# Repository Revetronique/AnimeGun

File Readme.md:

# アニメ銃 (ストロボスコープ式映写機)

## 目次
- [アニメ銃 (ストロボスコープ式映写機)](#アニメ銃-ストロボスコープ式映写機)
  - [目次](#目次)
- [概要](#概要)
- [準備するもの](#準備するもの)
  - [本体](#本体)
  - [円板](#円板)
- [使い方](#使い方)
  - [ボタン一覧](#ボタン一覧)
  - [基本](#基本)
  - [詳細](#詳細)
    - [パラメータ設定](#パラメータ設定)
    - [設定モード](#設定モード)
    - [設定方法](#設定方法)
    - [ファームウェア書き換え](#ファームウェア書き換え)
- [免責事項](#免責事項)
- [開発者](#開発者)
# 概要
影絵でアニメーション映像を見せる映写機です。

電源を入れて、壁に向かって引き金のボタンを押すことで、壁にアニメーションが映し出されます。

アニメのコマを描いた円板をモーターで回し、LEDのストロボ発光でアニメーションを移す仕組みです。
# 準備するもの
## 本体
- Arduino UNO R3
- LED
  - 単色を想定(主に白色)
  - パワーLED(5V, 1W or 3W)にも対応
- 専用シールド
  - [回路およびプリント基板(Eagle用)](./Circuit)
  - 回路の詳細については、[回路についてのドキュメント](./Docs/Document_Circuit.md)を参照
- 筐体
  - アクリル板(厚さ3mm)をレーザーカッターで切断して、各パーツを積み重ねて制作
  - 筐体用のフレームは[Frameフォルダ](./Frame)を参照
  - 詳細は、[筐体についてのドキュメント](./Docs/Document_Frame.md)を参照
  - **試作段階のため、回路が筐体に収まらないなどの問題が生じる可能性があります**
- ACアダプタ(出力：DC12V, 1A以上)
## 円板
詳細は[円板についてのドキュメント](./Docs/Document_Plate.md)を参照。
# 使い方

## ボタン一覧
1. **トリガー**：押すことでアニメを動かします(ストロボ発光+モーター駆動)
2. 7セグLED：設定モード([後述](#設定モード))やアニメに関するパラメータを表示
3. 機能ボタン：押すと設定モードを変更
4. **調節ノブ**：回すことでパラメータを調節

また、トグルスイッチでモーター回転の有効/無効を切り替えられます(右に倒すと有効)。ファームウェアの書き換え中など、モーターを回したくない時は左に倒してください。
## 基本
1. モーターにアニメ用の円板を付けます
2. 本体後ろのDCジャックに、上記のACアダプタから電源を供給
3. 銃口を壁に向けてトリガーを引くと、アニメーションが流れます
4. 調節ノブを回すと、アニメーションの速さを変えられます
## 詳細
### パラメータ設定
機能ボタンと調節ノブを使って、アニメーションに関する4種類のパラメータを調整できます。選択したパラメータと数値は7セグLEDで確認できます。
### 設定モード
パラメータの種類は以下の通り。
- sp(回転速度)：モーターの回転数(rpm)。数値は8~60
- dg(角度調節)：円板の角度調節。ずれの相殺に使います
- br(明るさ)：LEDの明るさ調整。0~25までの26段階
- fr(フレーム数)：アニメのコマ数
### 設定方法
起動時は、sp(回転速度)がセットされています。

ボタンを押すと、sp->dg->bf->fr の順に切り替わります。ボタンを押して0.5秒程度、選んだパラメータ名が7セグLEDに表示されます。

表示が数値に切り替わったら、調節ノブでパラメータを調節できます。
### ファームウェア書き換え
本体のファームウェア(Arduinoスケッチ)を書き換えたい場合は、背面のUSBコネクタでArduino IDEの入ったPCなどと接続します。ケーブルはUSB(ABタイプ)を使用します。
# 免責事項
- **使うときは人に向けないでください。特にパワーLEDを搭載する場合、失明の恐れがあります**
- 本体を振り回さないでください。ケガや破損の恐れがあります。
- モーターの回転中は、円板に触れないよう注意してください。思わぬケガの元となります。
- ファームウェア書き換え時は、書き込み用の機器と接続する前に、本体の電源を外してください。また、**接続中はトリガーを押さないでください**。
- 円板を付け替える際も、電源を外してから作業してください。
- 15V以上の電圧を絶対にかけないでください。
  - 出力電源は、12V,1A出力のACアダプタ推奨。
- 上記の項目の他、組み立て時や使用中などにおける利用者のあらゆる事故・不具合に対して、開発者は責任を負いません。

# 開発者
Revetronique
- [Web](https://revetronique.com/)
- [Twitter](https://twitter.com/Revetronique)
- [Instagram](https://www.instagram.com/revetronique/)

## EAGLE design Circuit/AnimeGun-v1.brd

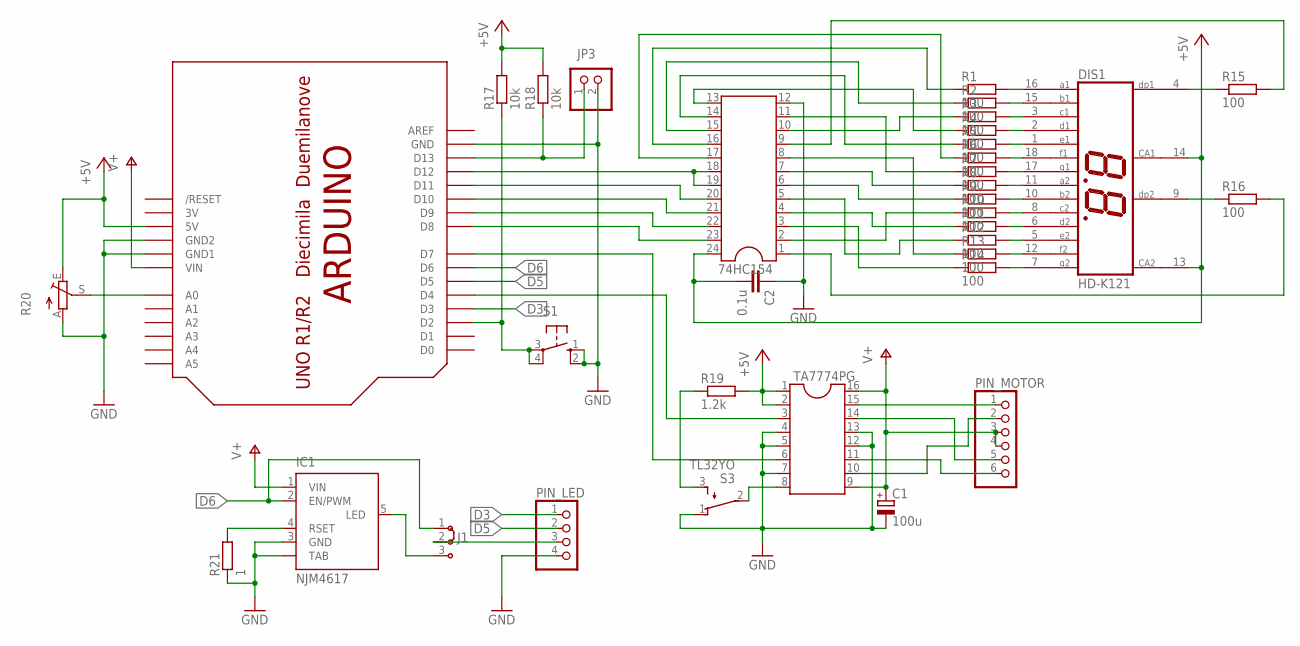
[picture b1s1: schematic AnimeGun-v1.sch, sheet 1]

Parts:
74HC154: DIL24-3
C1: 100u; 153CLV-0605
C2: 0.1u; C0603
DIS1: HD-K121; HDSP-R
IC1: NJM4617; TO263_5
J1: J2X2MM; 04C
JP3: PINHD-1X2; 1X02
PIN_LED: PINHD-1X4/90; 1X04/90
PIN_MOTOR: PINHD-1X6/90; 1X06/90
R1, R2, R3, R4, R5, R6, R7, R8, R9, R10, R12, R13, R14, R15, R16: 100; R0603
R11: R-EU_R0603; R0603
R17, R18: 10k; R0603
R19: 1.2k; R0603
R20: TRIM_EU-B25U; B25U
R21: 1; R0603
S1: 10-XX; B3F-10XX
S3: TL32YO; TL3XYO
TA7774PG: DIL16
U1: ARDUINO-NOHOLE

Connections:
3V: U1.3V
+5V: 74HC154.24, C2.2, DIS1.13 (CA2), DIS1.14 (CA1), R17.2, R18.2, R19.2, R20.E, TA7774PG.1, TA7774PG.2, U1.5V
D3: PIN_LED.1, U1.D3
D5: PIN_LED.2, U1.D5
D6: IC1.2 (EN/PWM), J1.1, U1.D6
GND: 74HC154.12, C1.-, C2.1, IC1.3 (GND), IC1.TAB, JP3.2, PIN_LED.4, R20.A, R21.1, S1.1 (S), S1.2 (S1), S3.1 (O), TA7774PG.4, TA7774PG.5, TA7774PG.7, TA7774PG.12, TA7774PG.13, U1.GND, U1.GND1, U1.GND2
unnamed: R17.1, S1.3, S1.4 (P1), U1.D2
unnamed: DIS1.16 (A1), R1.2
unnamed: DIS1.15 (B1), R2.2
unnamed: DIS1.3 (C1), R3.2
unnamed: DIS1.2 (D1), R4.2
unnamed: DIS1.1 (E1), R5.2
unnamed: DIS1.18 (F1), R6.2
unnamed: DIS1.17 (G1), R7.2
unnamed: DIS1.11 (A2), R8.2
unnamed: DIS1.10 (B2), R9.2
unnamed: DIS1.8 (C2), R10.2
unnamed: DIS1.6 (D2), R11.2
unnamed: DIS1.5 (E2), R12.2
unnamed: DIS1.12 (F2), R13.2
unnamed: DIS1.7 (G2), R14.2
unnamed: DIS1.4 (DP1), R15.1
unnamed: DIS1.9 (DP2), R16.1
unnamed: 74HC154.1, R16.2
unnamed: 74HC154.2, R10.1
unnamed: 74HC154.3, R14.1
unnamed: 74HC154.4, R11.1
unnamed: 74HC154.5, R12.1
unnamed: 74HC154.6, R9.1
unnamed: 74HC154.7, R8.1
unnamed: 74HC154.8, R13.1
unnamed: 74HC154.9, R15.2
unnamed: 74HC154.10, R3.1
unnamed: 74HC154.11, R7.1
unnamed: 74HC154.13, R4.1
unnamed: 74HC154.14, R5.1
unnamed: 74HC154.15, R2.1
unnamed: 74HC154.16, R1.1
unnamed: 74HC154.17, R6.1
unnamed: 74HC154.18, 74HC154.19, U1.D12
unnamed: TA7774PG.6, U1.D7
unnamed: 74HC154.20, U1.D11
unnamed: 74HC154.21, U1.D10
unnamed: 74HC154.22, U1.D9
unnamed: 74HC154.23, U1.D8
unnamed: TA7774PG.3, U1.D4
unnamed: JP3.1, R18.1, U1.D13
unnamed: S3.2, TA7774PG.8
unnamed: PIN_MOTOR.6, TA7774PG.11
unnamed: PIN_MOTOR.1, TA7774PG.15
unnamed: PIN_MOTOR.5, TA7774PG.14
unnamed: PIN_MOTOR.2, TA7774PG.10
unnamed: R19.1, S3.3 (S)
unnamed: R20.S, U1.A0
unnamed: IC1.4 (RSET), R21.2
unnamed: J1.2, PIN_LED.3
unnamed: IC1.5 (LED), J1.3
V+: C1.+, IC1.1 (VIN), PIN_MOTOR.3, PIN_MOTOR.4, TA7774PG.9, TA7774PG.16, U1.VIN

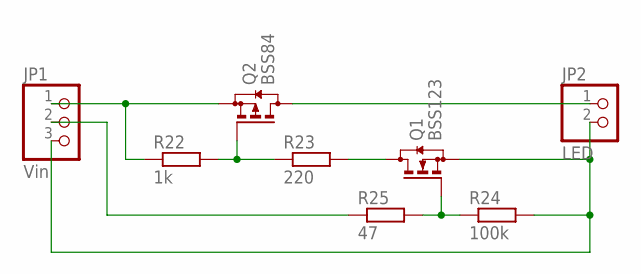
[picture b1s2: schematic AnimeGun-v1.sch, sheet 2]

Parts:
JP1: Vin; 1X03
JP2: LED; 1X02
Q1: BSS123; SOT23
Q2: BSS84; SOT23
R22: 1k; R2512
R23: 220; R2512
R24: 100k; R0603
R25: 47; R0603

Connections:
unnamed: Q2.1 (G), R22.2, R23.1
unnamed: JP1.1, Q2.2 (S), R22.1
unnamed: Q1.3 (D), R23.2
unnamed: JP2.1, Q2.3 (D)
unnamed: Q1.1 (G), R24.1, R25.2
unnamed: JP1.3, JP2.2, Q1.2 (S), R24.2
unnamed: JP1.2, R25.1

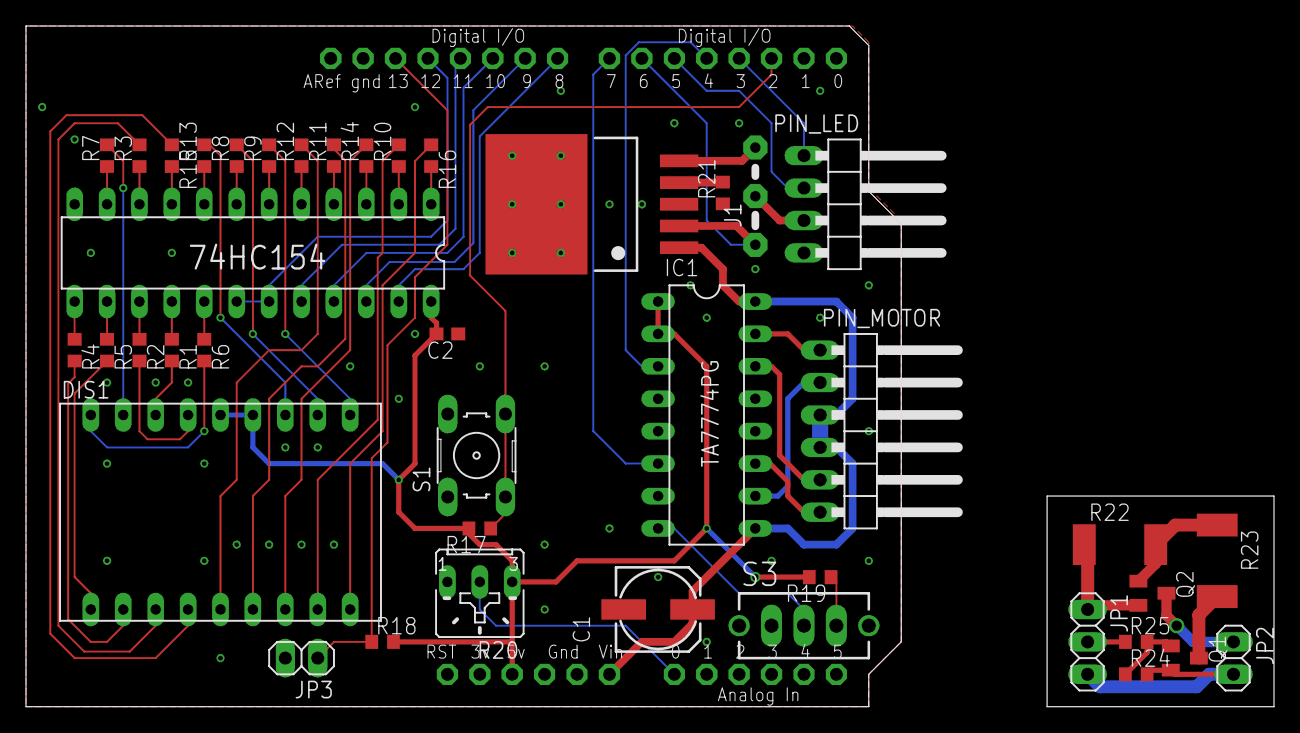
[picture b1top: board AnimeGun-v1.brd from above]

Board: 2 copper layers, 97.8 x 53.3 mm, 42 parts (0 on the bottom side), 64 nets.

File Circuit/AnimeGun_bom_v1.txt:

Partlist exported from C:/Users/kokit/OneDrive/ドキュメント/EAGLE/projects/AnimeGun/AnimeGun-v1.sch at 2020/11/28 15:33

Part      Value          Device             Package        Description                                     MF MPN           OC_FARNELL OC_NEWARK POPULARITY SPICEPREFIX
74HC154                  DIL24-3            DIL24-3        Dual In Line                                                                          0                     
C1        100u           CPOL-EU153CLV-0605 153CLV-0605    POLARIZED CAPACITOR, European symbol                                                  5          C          
C2        0.1u           C-EUC0603          C0603          CAPACITOR, European symbol                                                            73         C          
DIS1      HD-K121        HD-K121            HDSP-R         LED DISPLAY                                                      unknown    unknown   0                     
IC1       NJM4617        NJM4617            TO263_5        1A Constant-Current LED Driver with PWM Dimming    CAT4101TV-T75 1718452    08R5264                         
J1                       J2X2MM             04C            Jumper switch 2 x 2.5 mm                                                                                    
JP1       Vin            PINHD-1X3          1X03           PIN HEADER                                                                            92                    
JP2       LED            PINHD-1X2          1X02           PIN HEADER                                                                            98                    
JP3                      PINHD-1X2          1X02           PIN HEADER                                                                            98                    
PIN_LED                  PINHD-1X4/90       1X04/90        PIN HEADER                                                                            9                     
PIN_MOTOR                PINHD-1X6/90       1X06/90        PIN HEADER                                                                            10                    
Q1        BSS123         BSS123             SOT23          N-CHANNEL MOS FET                                                                                           
Q2        BSS84          BSS84              SOT23          P-CHANNEL MOS FET                                                                                           
R1        100            R-EU_R0603         R0603          RESISTOR, European symbol                                                             70         R          
R2        100            R-EU_R0603         R0603          RESISTOR, European symbol                                                             70         R          
R3        100            R-EU_R0603         R0603          RESISTOR, European symbol                                                             70         R          
R4        100            R-EU_R0603         R0603          RESISTOR, European symbol                                                             70         R          
R5        100            R-EU_R0603         R0603          RESISTOR, European symbol                                                             70         R          
R6        100            R-EU_R0603         R0603          RESISTOR, European symbol                                                             70         R          
R7        100            R-EU_R0603         R0603          RESISTOR, European symbol                                                             70         R          
R8        100            R-EU_R0603         R0603          RESISTOR, European symbol                                                             70         R          
R9        100            R-EU_R0603         R0603          RESISTOR, European symbol                                                             70         R          
R10       100            R-EU_R0603         R0603          RESISTOR, European symbol                                                             70         R          
R11                      R-EU_R0603         R0603          RESISTOR, European symbol                                                             70         R          
R12       100            R-EU_R0603         R0603          RESISTOR, European symbol                                                             70         R          
R13       100            R-EU_R0603         R0603          RESISTOR, European symbol                                                             70         R          
R14       100            R-EU_R0603         R0603          RESISTOR, European symbol                                                             70         R          
R15       100            R-EU_R0603         R0603          RESISTOR, European symbol                                                             70         R          
R16       100            R-EU_R0603         R0603          RESISTOR, European symbol                                                             70         R          
R17       10k            R-EU_R0603         R0603          RESISTOR, European symbol                                                             70         R          
R18       10k            R-EU_R0603         R0603          RESISTOR, European symbol                                                             70         R          
R19       1.2k           R-EU_R0603         R0603          RESISTOR, European symbol                                                             70         R          
R20                      TRIM_EU-B25U       B25U           POTENTIOMETER                                                                                               
R21       1              R-EU_R0603         R0603          RESISTOR, European symbol                                                             70         R          
R22       1k             R-EU_R2512         R2512          RESISTOR, European symbol                                                             0          R          
R23       220            R-EU_R2512         R2512          RESISTOR, European symbol                                                             0          R          
R24       100k           R-EU_R0603         R0603          RESISTOR, European symbol                                                             70         R          
R25       47             R-EU_R0603         R0603          RESISTOR, European symbol                                                             70         R          
S1                       10-XX              B3F-10XX       OMRON SWITCH                                       B3F-1000      176432     36M3542   72                    
S3        TL32YO         TL32YO             TL3XYO         TINY SWITCH ON - MOM                                                                  1                     
TA7774PG                 DIL16              DIL16          Dual In Line / Socket                                                                 2                     
U1        ARDUINO-NOHOLE ARDUINO-NOHOLE     ARDUINO-NOHOLE Arduino Diecimila/Duemilanove

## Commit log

2020-11-26 First Commit
    [add] add files: firmware(Arduino sketch), circuit schematics and housing frame
2020-11-29 Add Readme and document files
    [add] Readme.md and Documents
2020-11-29 fix document file
    [fix] revise Document_Circuit.md
2020-11-29 revise document file
    [fix] revise Readme.md
